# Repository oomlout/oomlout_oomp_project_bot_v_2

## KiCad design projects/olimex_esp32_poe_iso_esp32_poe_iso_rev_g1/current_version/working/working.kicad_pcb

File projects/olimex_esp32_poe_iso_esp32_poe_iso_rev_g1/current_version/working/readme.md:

# esp32_poe_iso
 
## summary 
* id: olimex_esp32_poe_iso_esp32_poe_iso_rev_g1
* user: olimex
* name: esp32_poe_iso
* board: esp32_poe_iso_rev_g1
* repo: https://github.com/OLIMEX/ESP32-POE-ISO
* src_file_repo_kicad_pcb: HARDWARE/ESP32-PoE-ISO-Rev.G1/ESP32-PoE-ISO_Rev_G1.kicad_pcb
* src_file_repo_kicad_pcb_link: https://github.com/OLIMEX/ESP32-POE-ISO/tree/master/HARDWARE/ESP32-PoE-ISO-Rev.G1/ESP32-PoE-ISO_Rev_G1.kicad_pcb

* src_file_repo_sch: HARDWARE/ESP32-PoE-ISO-Rev.G1/ESP32-PoE-ISO_Rev_G1.sch
* src_file_repo_sch_link: https://github.com/OLIMEX/ESP32-POE-ISO/tree/master/HARDWARE/ESP32-PoE-ISO-Rev.G1/ESP32-PoE-ISO_Rev_G1.sch
* full details link: https://github.com/oomlout/oomlout_oomp_project_bot_v_2/tree/main/projects/olimex_esp32_poe_iso_esp32_poe_iso_rev_g1/current_version/working

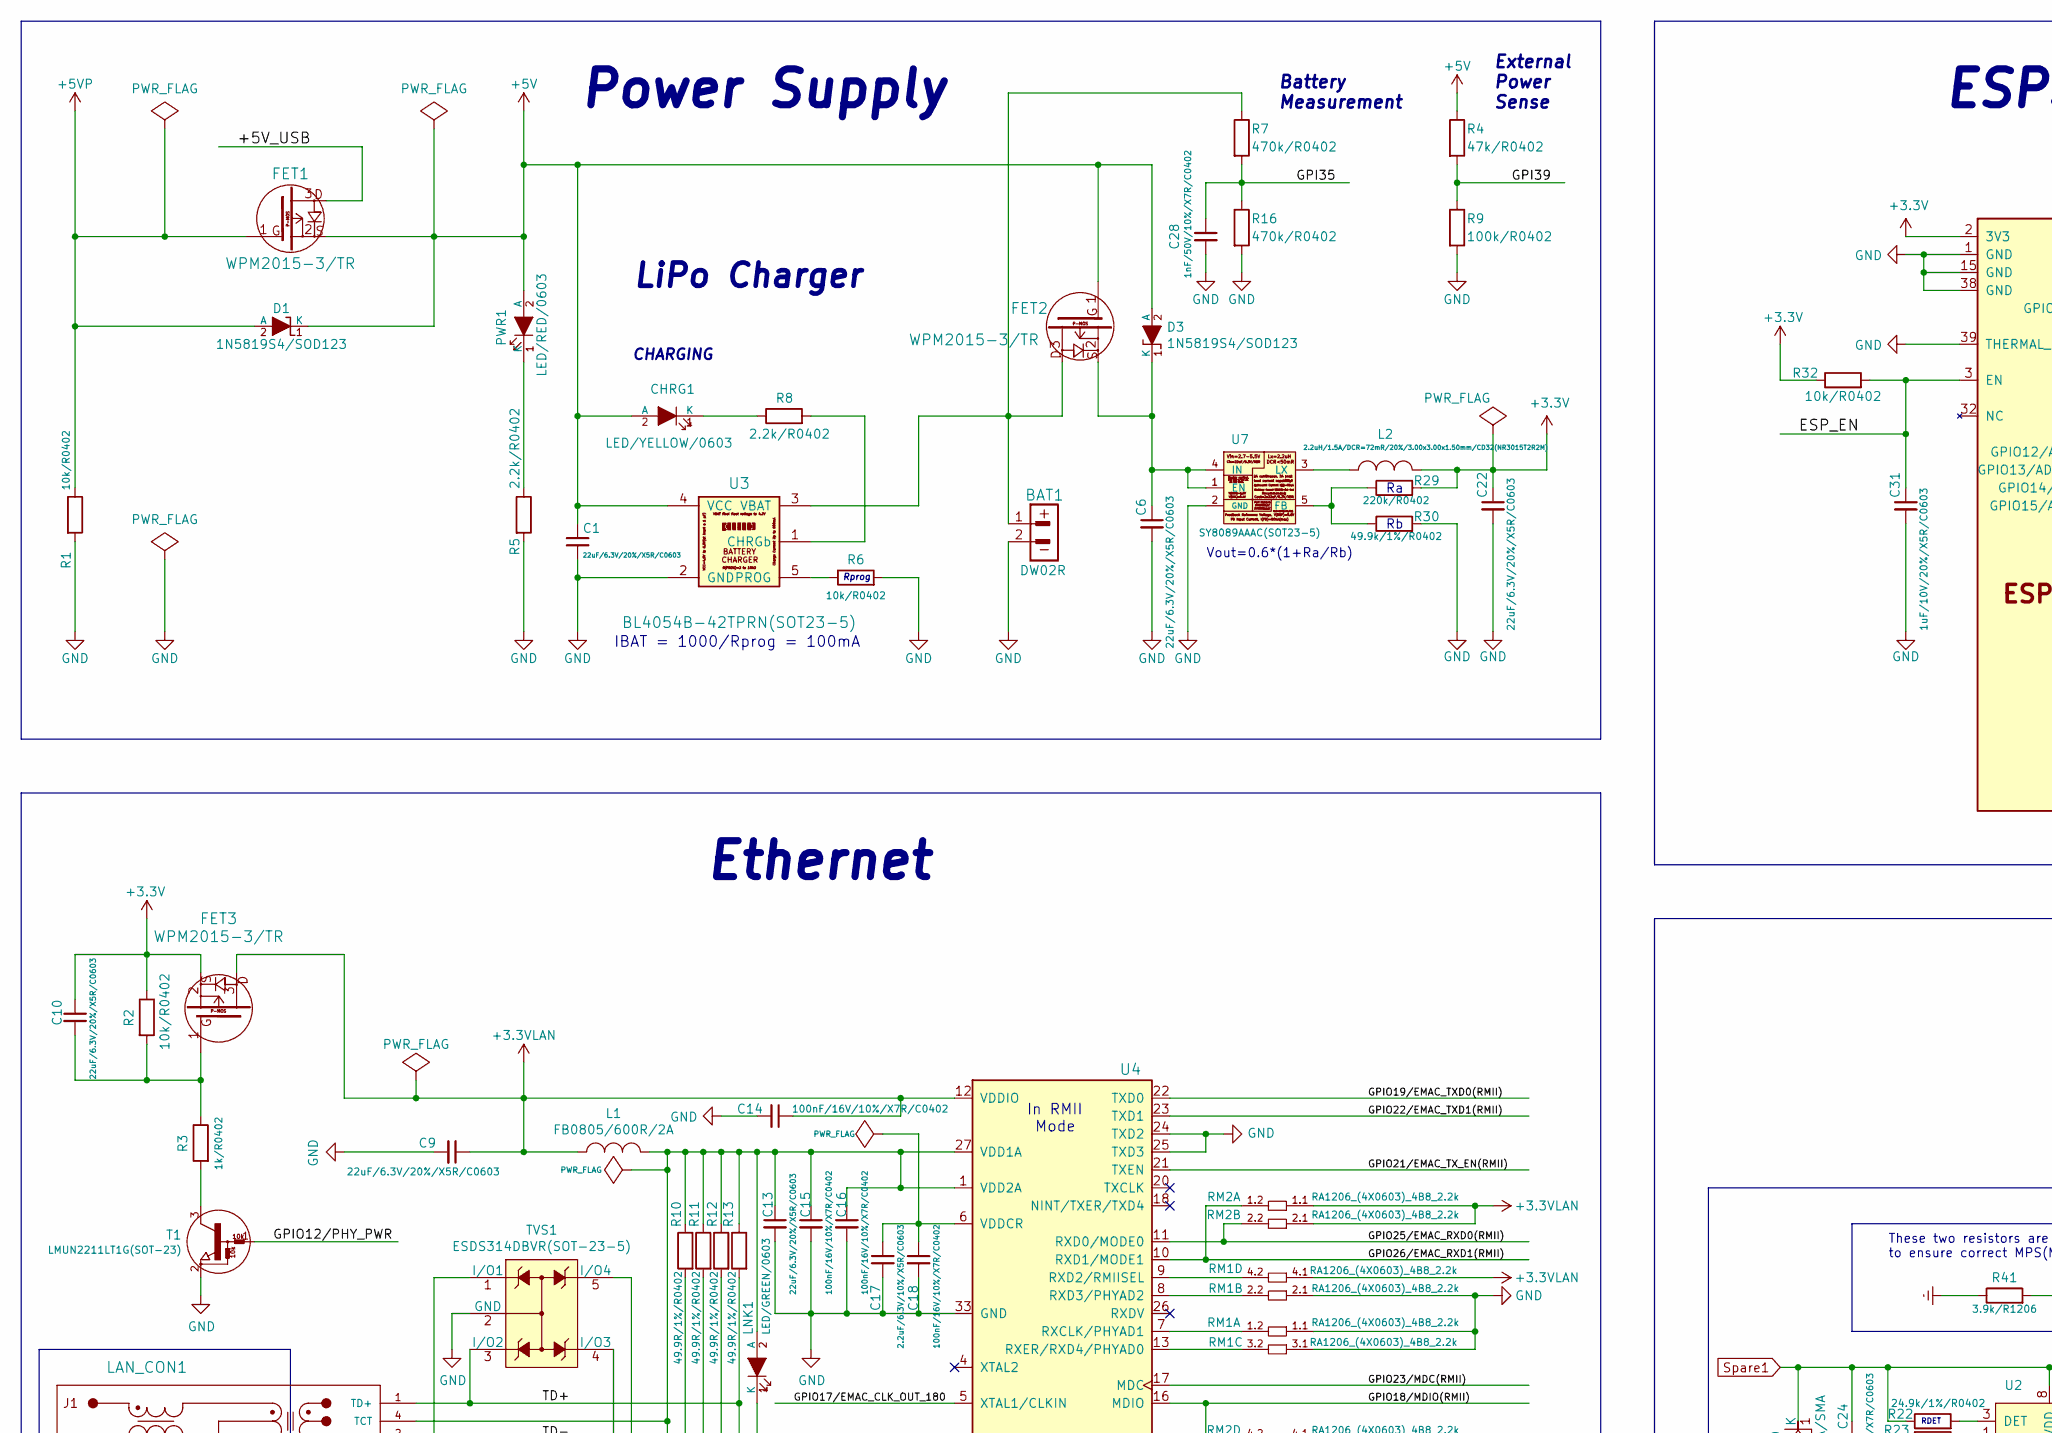
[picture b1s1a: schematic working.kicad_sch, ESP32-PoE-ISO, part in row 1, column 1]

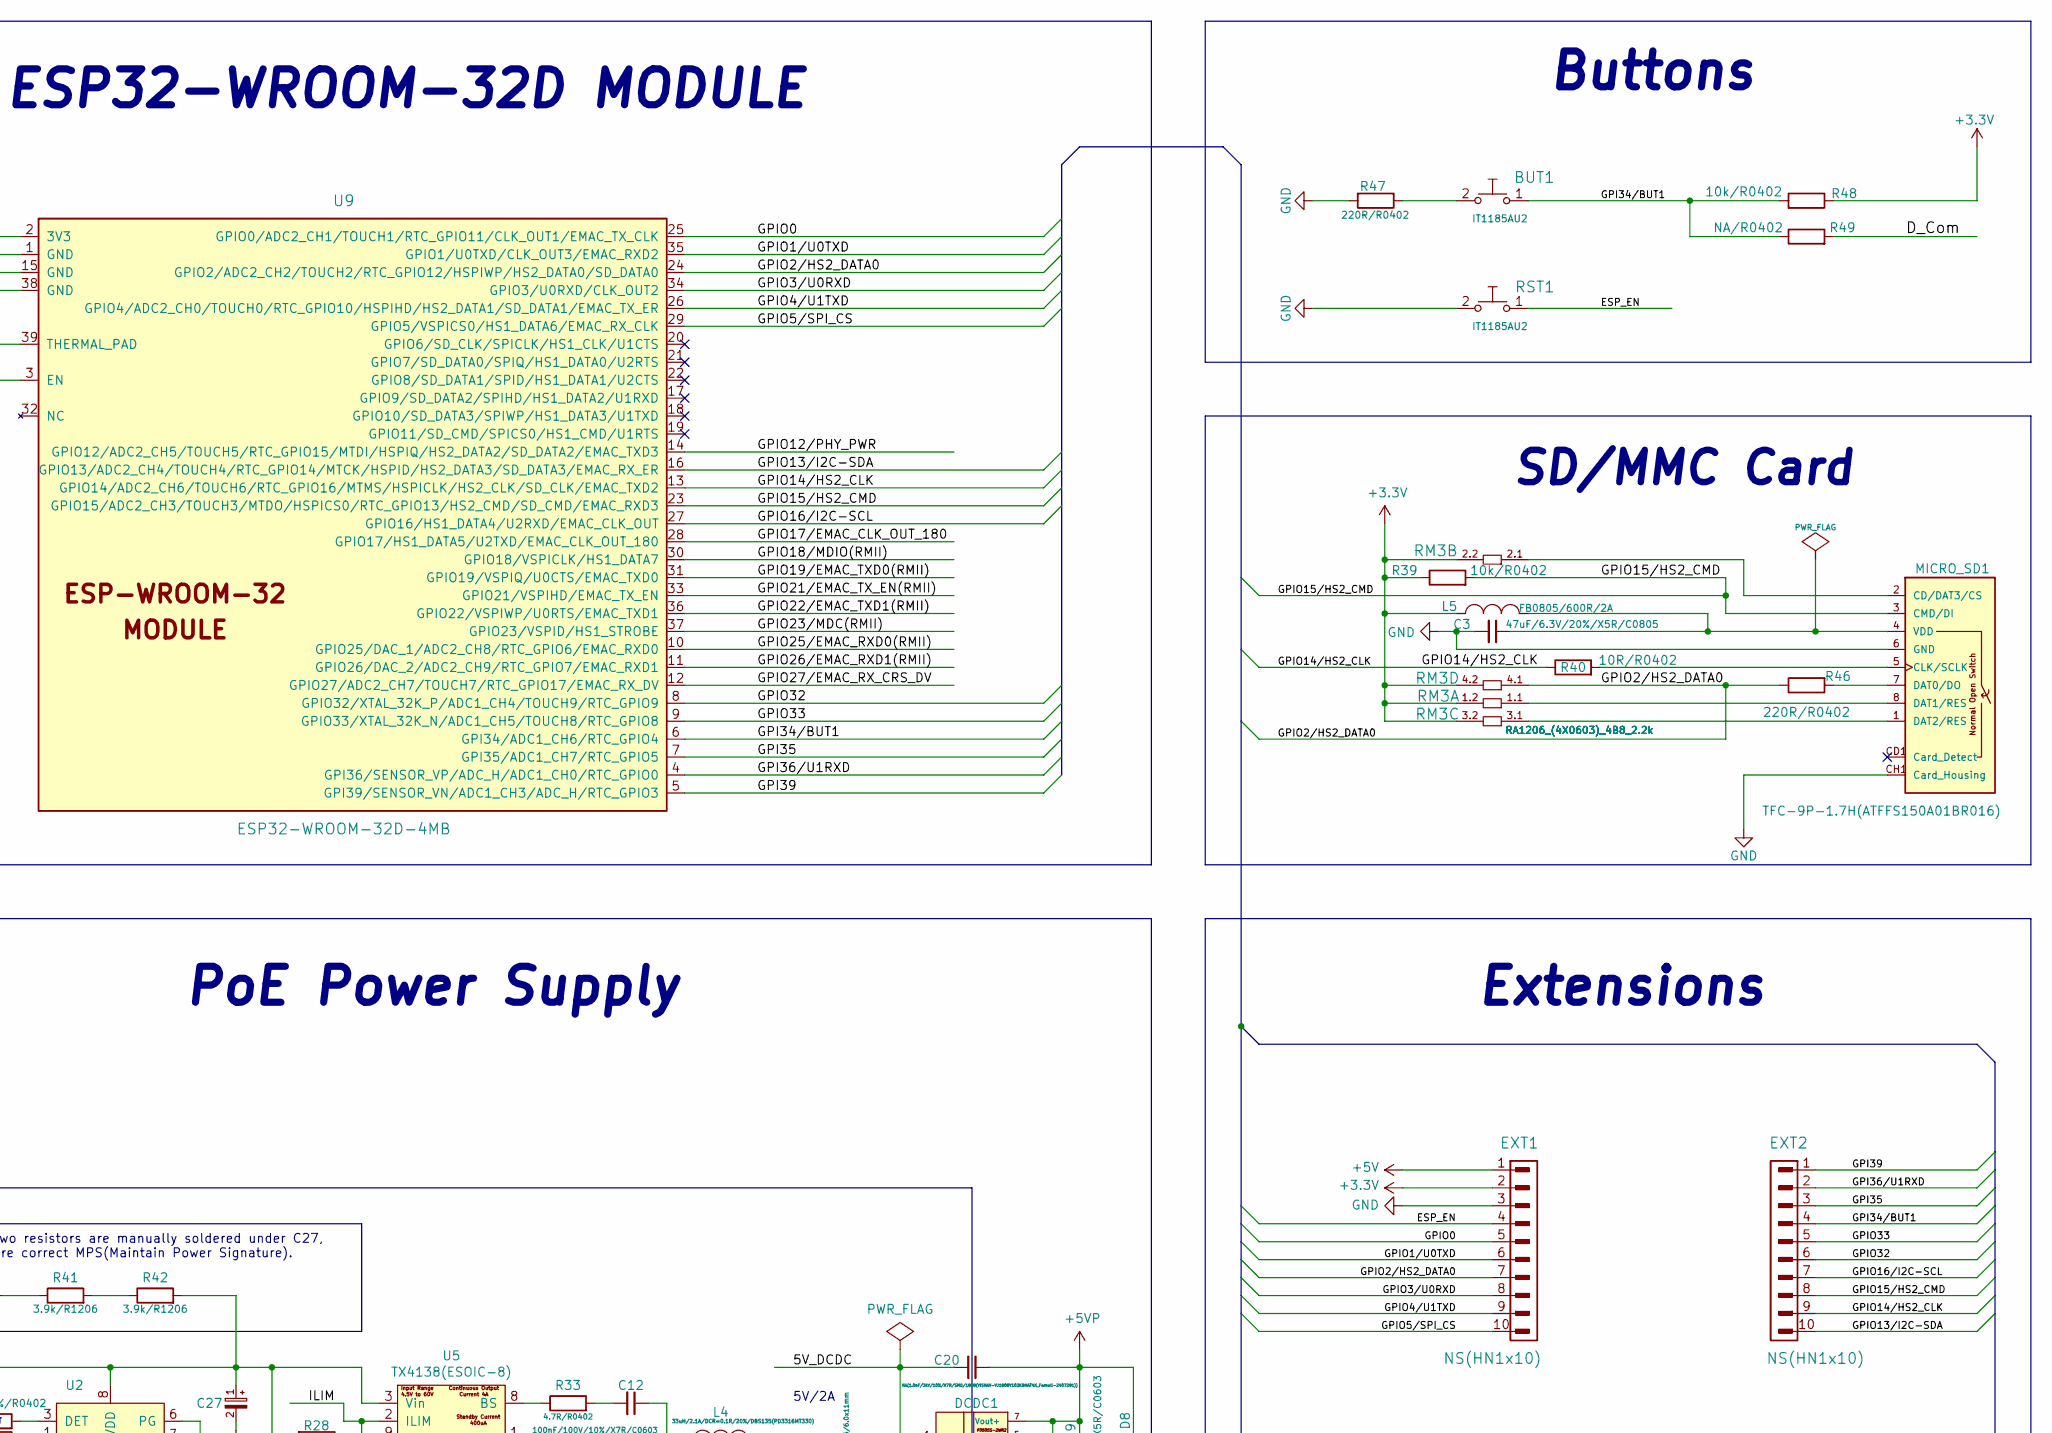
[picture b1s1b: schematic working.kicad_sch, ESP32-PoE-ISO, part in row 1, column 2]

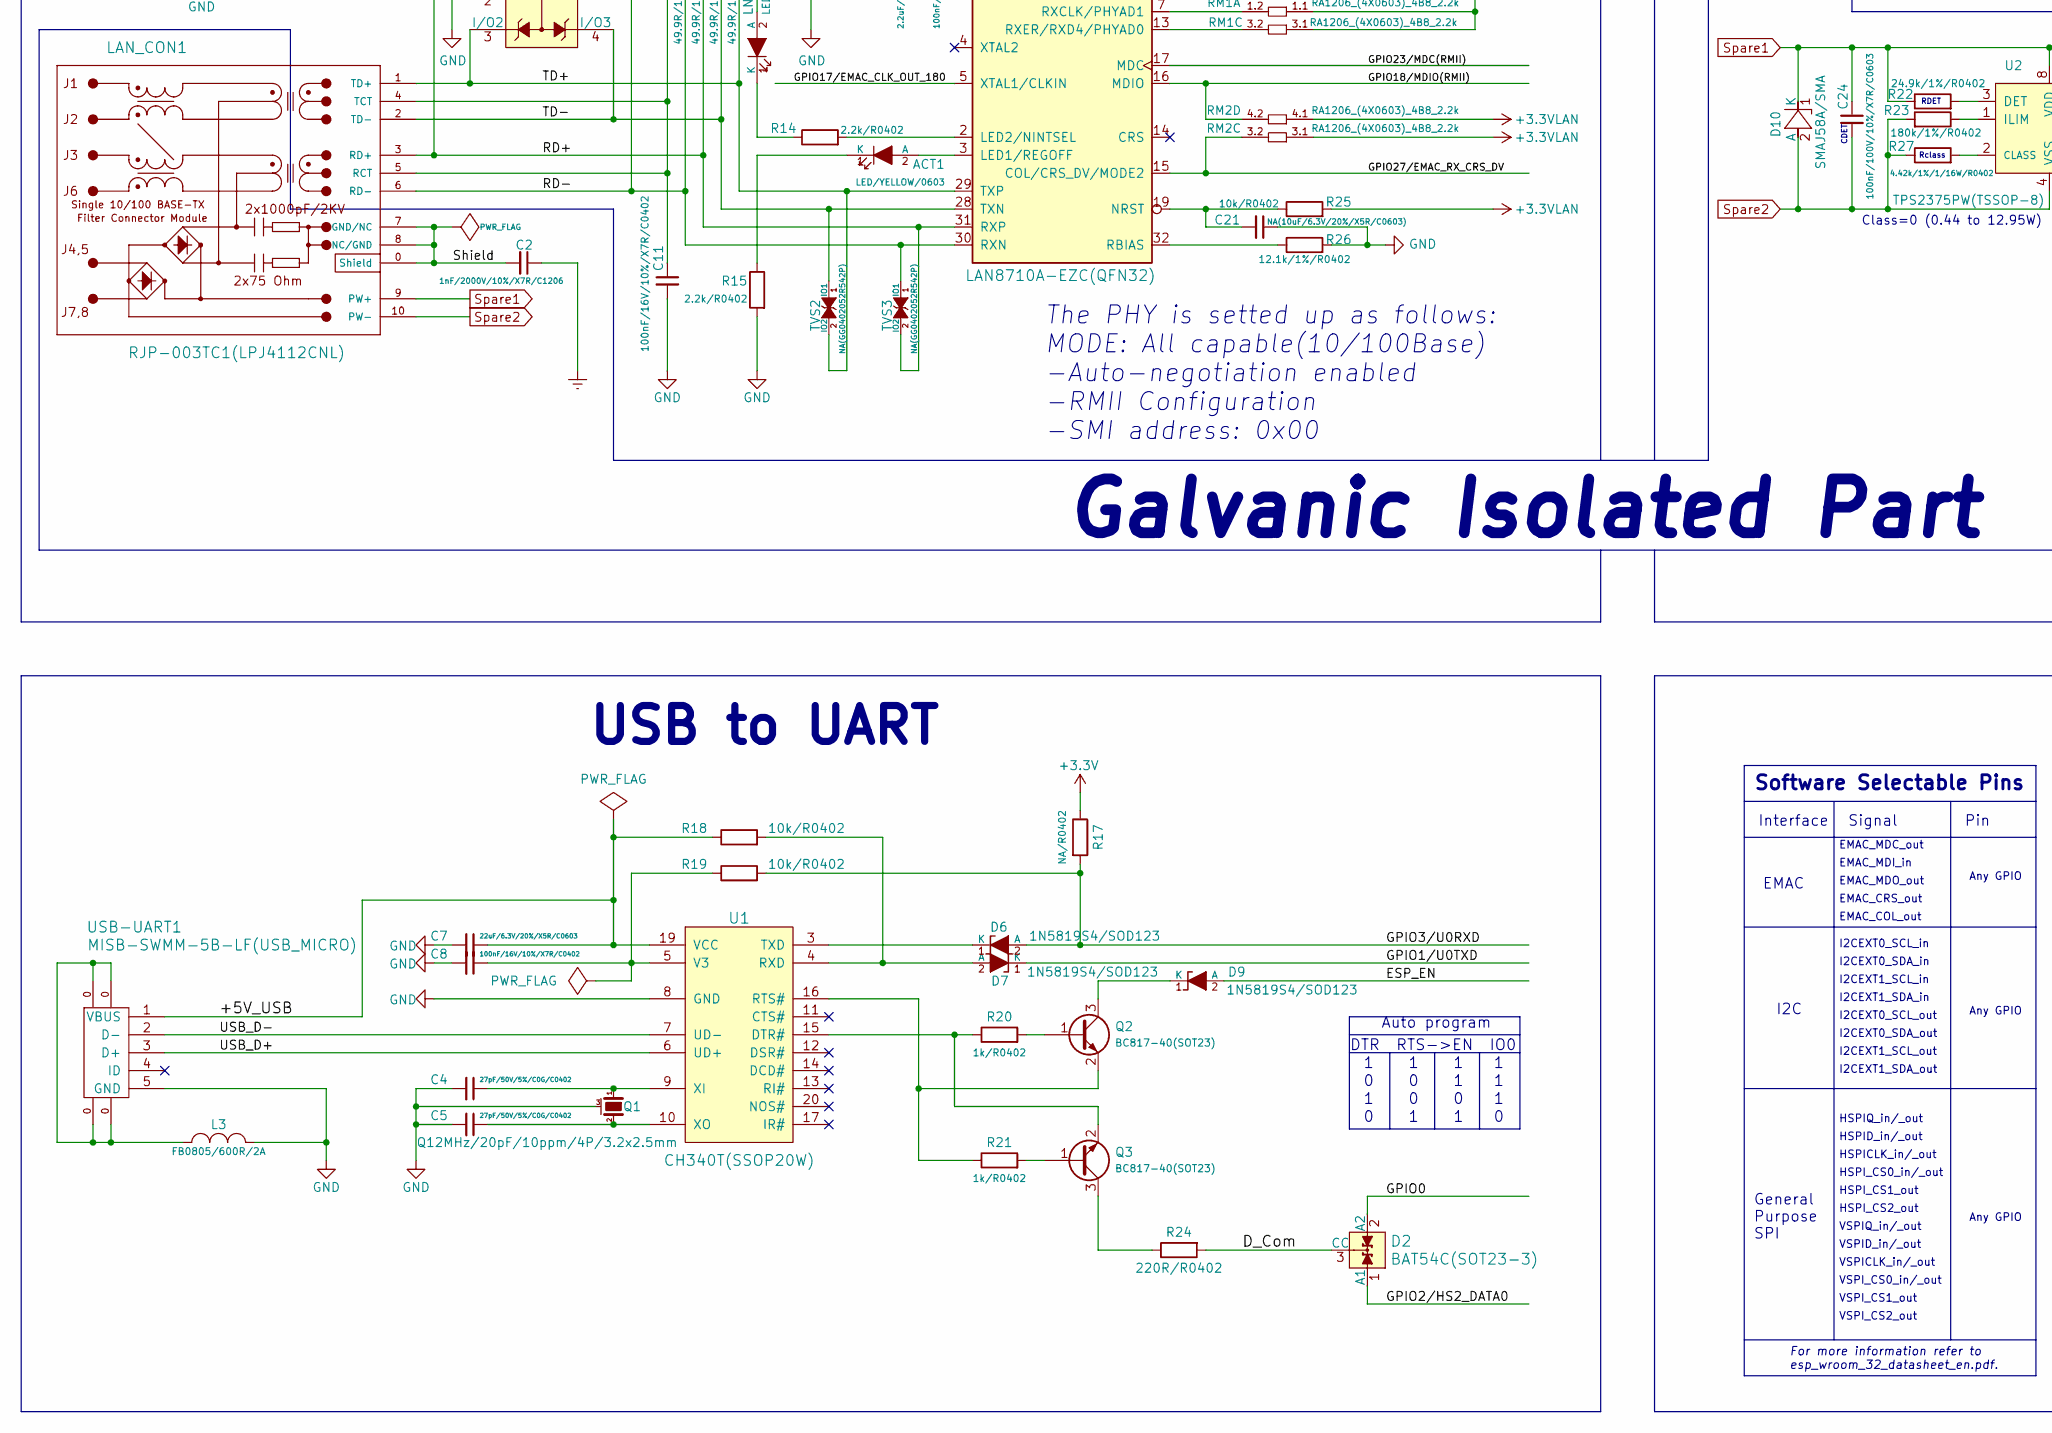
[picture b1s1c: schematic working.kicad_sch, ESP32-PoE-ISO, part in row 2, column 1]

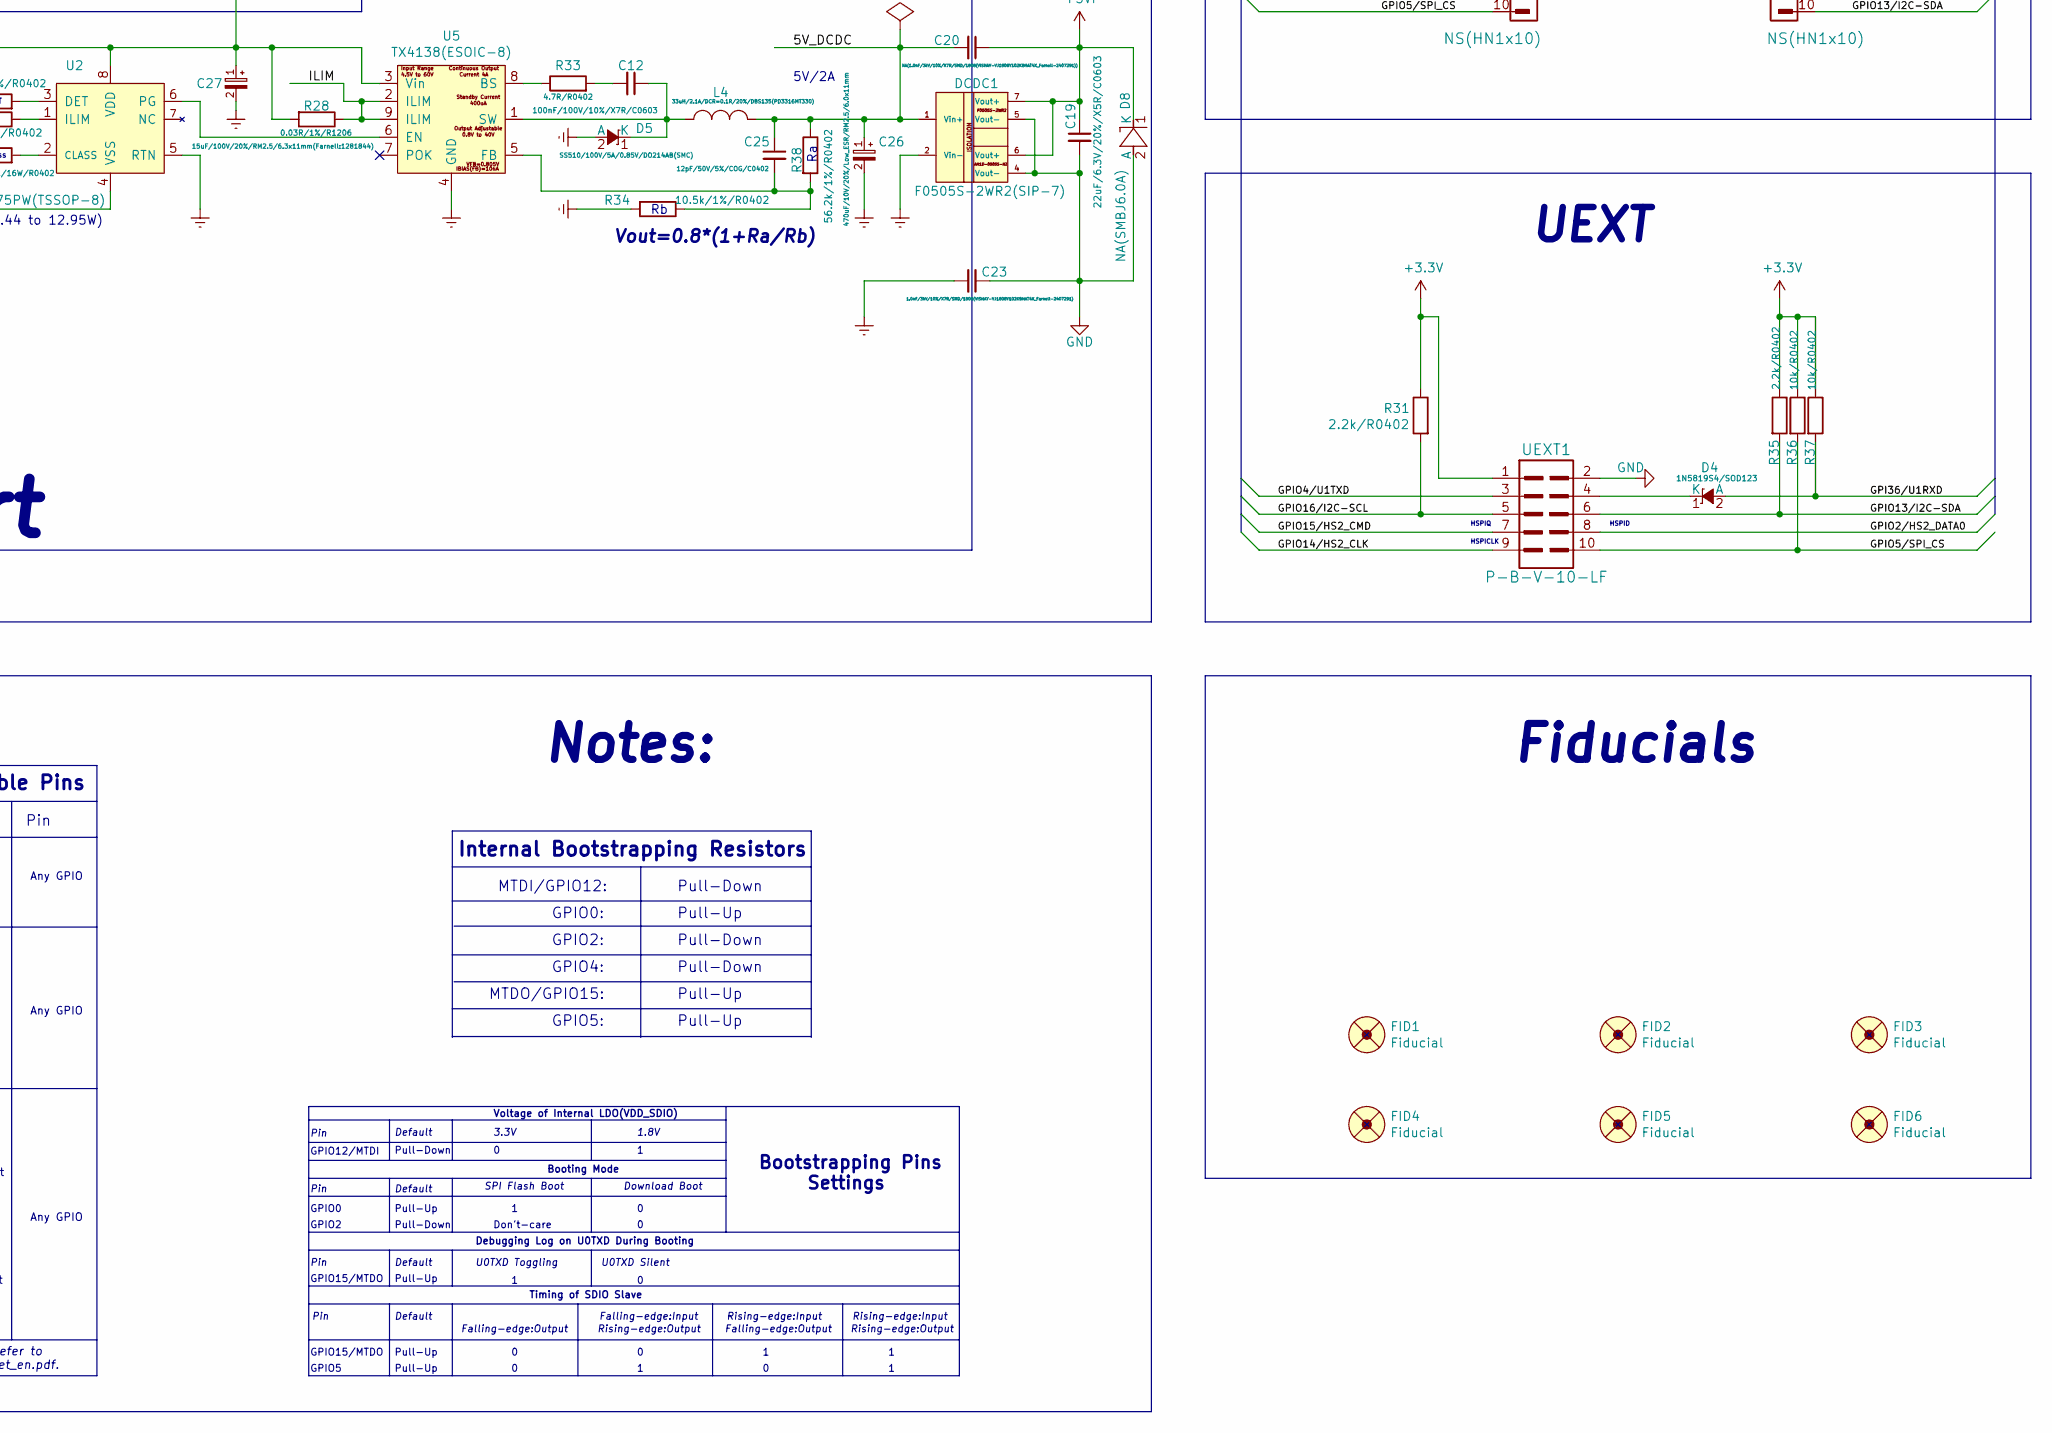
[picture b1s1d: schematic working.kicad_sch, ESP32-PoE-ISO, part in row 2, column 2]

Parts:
ACT1: LED/YELLOW/0603; LED_0603_KA
BAT1: DW02R; LIPO_BAT-CON2DW02R
BUT1: IT1185AU2; IT1185AU2_V2
C1, C6, C7, C9, C10, C13, C19, C22: 22uF/6.3V/20%/X5R/C0603; C_0603_5MIL_DWS
C2: 1nF/2000V/10%/X7R/C1206; C_1206_5MIL_DWS_ISO
C3: 47uF/6.3V/20%/X5R/C0805; C_0805_5MIL_DWS
C4, C5: 27pF/50V/5%/C0G/C0402; C_0402_5MIL_DWS
C8, C11, C14, C15, C16, C18: 100nF/16V/10%/X7R/C0402; C_0402_5MIL_DWS
C12, C24: 100nF/100V/10%/X7R/C0603; C_0603_5MIL_DWS
C17: 2.2uF/6.3V/10%/X5R/C0603; C_0603_5MIL_DWS
C20: NA(1.0nF/3kV/10%/X7R/SMD/1808(VISHAY-VJ1808Y102KB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; C_1808(4520)_5MIL_DWS_ISO
C21: NA(10uF/6.3V/20%/X5R/C0603); C_0603_5MIL_DWS
C23: 1.0nF/3kV/10%/X7R/SMD/1808(VISHAY-VJ1808Y102KBHAT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; C_1808(4520)_5MIL_DWS_ISO
C25: 12pF/50V/5%/COG/C0402; C_0402_5MIL_DWS
C26: 470uF/10V/20%/Low_ESR/RM2.5/6.0x11mm; CPOL-RM2.5mm_6.3x11mm_PTH
C27: 15uF/100V/20%/RM2.5/6.3x11mm(Farnell:1281844); CPOL-RM2.5mm_6.3x11mm_PTH
C28: 1nF/50V/10%/X7R/C0402; C_0402_5MIL_DWS
C31: 1uF/10V/20%/X5R/C0603; C_0603_5MIL_DWS
CHRG1: LED/YELLOW/0603; LED_0603_KA
D1, D3, D4, D6, D7, D9: 1N5819S4/SOD123; SOD-123_1C-2A_KA
D2: BAT54C(SOT23-3); SOT23-3
D5: SS510/100V/5A/0.85V/DO214AB(SMC); DO214AB(SMC)_1(K)-2(A)
D8: NA(SMBJ6.0A); DO214AA_1(K)-2(A)
D10: SMAJ58A/SMA; SMA-KA
DCDC1: F0505S-2WR2(SIP-7); SIP-7_Universal
EXT1, EXT2: NS(HN1x10); HN1x10
FET1, FET2, FET3: WPM2015-3/TR; SOT23
FID1, FID2, FID3, FID4, FID5, FID6: Fiducial; Fiducial1x3
L1, L3, L5: FB0805/600R/2A; L_0805_5MIL_DWS
L2: 2.2uH/1.5A/DCR=72mR/20%/3.00x3.00x1.50mm/CD32(NR3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; CD32
L4: 33uH/2.1A/DCR=0.1R/20%/DBS135(PD3316MT330); DBS135
LAN_CON1: RJP-003TC1(LPJ4112CNL)
LNK1: LED/GREEN/0603; LED_0603_KA
MICRO_SD1: TFC-9P-1.7H(ATFFS150A01BR016); uSD(TFC-9P-1.xH(ATFFS150A01BR016))
PWR1: LED/RED/0603; LED_0603_KA
Q1: Q12MHz/20pF/10ppm/4P/3.2x2.5mm; TSX-3.2x2.5mm_GND(3)
Q2, Q3: BC817-40(SOT23); SOT23
R1, R2, R6, R18, R19, R25, R32, R36, R37, R39, R48: 10k/R0402; R_0402_5MIL_DWS
R3, R20, R21: 1k/R0402; R_0402_5MIL_DWS
R4: 47k/R0402; R_0402_5MIL_DWS
R5, R8, R14, R15, R31, R35: 2.2k/R0402; R_0402_5MIL_DWS
R7, R16: 470k/R0402; R_0402_5MIL_DWS
R9: 100k/R0402; R_0402_5MIL_DWS
R10, R11, R12, R13: 49.9R/1%/R0402; R_0402_5MIL_DWS
R17, R49: NA/R0402; R_0402_5MIL_DWS
R22: 24.9k/1%/R0402; R_0402_5MIL_DWS
R23: 180k/1%/R0402; R_0402_5MIL_DWS
R24, R46, R47: 220R/R0402; R_0402_5MIL_DWS
R26: 12.1k/1%/R0402; R_0402_5MIL_DWS
R27: 4.42k/1%/1/16W/R0402; R_0402_5MIL_DWS
R28: 0.03R/1%/R1206; R_1206_5MIL_DWS
R29: 220k/R0402; R_0402_5MIL_DWS
R30: 49.9k/1%/R0402; R_0402_5MIL_DWS
R33: 4.7R/R0402; R_0402_5MIL_DWS
R34: 10.5k/1%/R0402; R_0402_5MIL_DWS
R38: 56.2k/1%/R0402; R_0402_5MIL_DWS
R40: 10R/R0402; R_0402_5MIL_DWS
R41, R42: 3.9k/R1206; R_1206_5MIL_DWS
RM1, RM2, RM3: RA1206_(4X0603)_4B8_2.2k; R_MATRIX_4
RST1: IT1185AU2; IT1185AU2_V2
T1: LMUN2211LT1G(SOT-23); SOT23
TVS1: ESDS314DBVR(SOT-23-5); SOT-23-5
TVS2, TVS3: NA(GG0402052R542P); D_0402_5MIL_DWS
U1: CH340T(SSOP20W); SSOP-20W
U2: TPS2375PW(TSSOP-8); TSSOP-8_Pitch-0.65mm_Dimensions-4.40x3.00x1.20mm
U3: BL4054B-42TPRN(SOT23-5); SOT-23-5
U4: LAN8710A-EZC(QFN32); QFN32_EP(33)_5.00x5.00x0.90mm_Pitch_0.50mm
U5: TX4138(ESOIC-8); ESOIC-8
U7: SY8089AAAC(SOT23-5); SOT-23-5
U9: ESP32-WROOM-32D-4MB; ESP-WROOM-32_MODULE
UEXT1: P-B-V-10-LF; GBH-254-SMT-10
USB-UART1: MISB-SWMM-5B-LF(USB_MICRO); USB-MICRO_MISB-SWMM-5B_LF

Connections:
+3.3VLAN: C9.1, C14.1, FET3.3, L1.1, R25.2, RM1.4.1, RM2.1.1, RM2.2.1, RM2.3.1, RM2.4.1, U4.12 (VDDIO)
+3V3: C10.1, C22.1, EXT1.2, FET3.2, L2.2, L5.1, R2.1, R17.1, R29.2, R31.1, R32.1, R35.1, R36.1, R37.1, R39.1, R48.1, RM3.1.2, RM3.2.2, RM3.3.2, RM3.4.2, U9.2 (3V3), UEXT1.1
+5V: C1.1, CHRG1.2 (A), D1.1 (K), D3.2 (A), EXT1.1, FET1.2, FET2.1, PWR1.2 (A), R4.1, U3.4 (VCC)
+5VP: C19.1, C20.1, D1.2 (A), D8.1 (K), DCDC1.6 (Vout+), DCDC1.7 (Vout+), FET1.1, R1.1
/5V_DCDC: C20.2, C25.1, C26.1 (+), DCDC1.1 (Vin+), L4.2, R38.1
/+5V_USB: C7.1, FET1.3, R18.1, U1.19 (VCC), USB-UART1.1 (VBUS)
/D_Com: D2.3 (CC), R24.2, R49.2
/ESP_EN: C31.1, D9.2 (A), EXT1.4, R32.2, RST1.1, U9.3 (EN)
/GPI34/BUT1: BUT1.1, EXT2.4, R48.2, R49.1, U9.6 (GPI34/ADC1_CH6/RTC_GPIO4)
/GPI35: C28.1, EXT2.3, R7.2, R16.1, U9.7 (GPI35/ADC1_CH7/RTC_GPIO5)
/GPI36/U1RXD: D4.2 (A), EXT2.2, R37.2, U9.4 (GPI36/SENSOR_VP/ADC_H/ADC1_CH0/RTC_GPIO0)
/GPI39: EXT2.1, R4.2, R9.1, U9.5 (GPI39/SENSOR_VN/ADC1_CH3/ADC_H/RTC_GPIO3)
/GPIO0: D2.2 (A2), EXT1.5, U9.25 (GPIO0/ADC2_CH1/TOUCH1/RTC_GPIO11/CLK_OU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)
/GPIO1/U0TXD: D7.1 (K), EXT1.6, U9.35 (GPIO1/U0TXD/CLK_OUT3/EMAC_RXD2)
/GPIO2/HS2_DATA0: D2.1 (A1), EXT1.7, R46.1, RM3.4.1, U9.24 (GPIO2/ADC2_CH2/TOUCH2/RTC_GPIO12/HSPIWP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), UEXT1.8
/GPIO3/U0RXD: D6.2 (A), EXT1.8, R17.2, R19.2, U9.34 (GPIO3/U0RXD/CLK_OUT2)
/GPIO4/U1TXD: EXT1.9, U9.26 (GPIO4/ADC2_CH0/TOUCH0/RTC_GPIO10/HSPIHD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), UEXT1.3
/GPIO5/SPI_CS: EXT1.10, R36.2, U9.29 (GPIO5/VSPICS0/HS1_DATA6/EMAC_RX_CLK), UEXT1.10
/GPIO12/PHY_PWR: T1.1 (B), U9.14 (GPIO12/ADC2_CH5/TOUCH5/RTC_GPIO15/MTDI/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)
/GPIO13/I2C-SDA: EXT2.10, R35.2, U9.16 (GPIO13/ADC2_CH4/TOUCH4/RTC_GPIO14/MTCK/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), UEXT1.6
/GPIO14/HS2_CLK: EXT2.9, R40.1, U9.13 (GPIO14/ADC2_CH6/TOUCH6/RTC_GPIO16/MTMS/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), UEXT1.9
/GPIO15/HS2_CMD: EXT2.8, MICRO_SD1.3 (CMD/DI), R39.2, U9.23 (GPIO15/ADC2_CH3/TOUCH3/MTDO/HSPICS0/RTC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), UEXT1.7
/GPIO16/I2C-SCL: EXT2.7, R31.2, U9.27 (GPIO16/HS1_DATA4/U2RXD/EMAC_CLK_OUT), UEXT1.5
/GPIO17/EMAC_CLK_OUT_180: U4.5 (XTAL1/CLKIN), U9.28 (GPIO17/HS1_DATA5/U2TXD/EMAC_CLK_OUT_180)
/GPIO18/MDIO(RMII): RM2.4.2, U4.16 (MDIO), U9.30 (GPIO18/VSPICLK/HS1_DATA7)
/GPIO19/EMAC_TXD0(RMII): U4.22 (TXD0), U9.31 (GPIO19/VSPIQ/U0CTS/EMAC_TXD0)
/GPIO21/EMAC_TX_EN(RMII): U4.21 (TXEN), U9.33 (GPIO21/VSPIHD/EMAC_TX_EN)
/GPIO22/EMAC_TXD1(RMII): U4.23 (TXD1), U9.36 (GPIO22/VSPIWP/U0RTS/EMAC_TXD1)
/GPIO23/MDC(RMII): U4.17 (MDC), U9.37 (GPIO23/VSPID/HS1_STROBE)
/GPIO25/EMAC_RXD0(RMII): RM2.2.2, U4.11 (RXD0/MODE0), U9.10 (GPIO25/DAC_1/ADC2_CH8/RTC_GPIO6/EMAC_RX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)
/GPIO26/EMAC_RXD1(RMII): RM2.1.2, U4.10 (RXD1/MODE1), U9.11 (GPIO26/DAC_2/ADC2_CH9/RTC_GPIO7/EMAC_RX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)
/GPIO27/EMAC_RX_CRS_DV: RM2.3.2, U4.15 (COL/CRS_DV/MODE2), U9.12 (GPIO27/ADC2_CH7/TOUCH7/RTC_GPIO17/EMAC_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)
/GPIO32: EXT2.6, U9.8 (GPIO32/XTAL_32K_P/ADC1_CH4/TOUCH9/RTC_G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)
/GPIO33: EXT2.5, U9.9 (GPIO33/XTAL_32K_N/ADC1_CH5/TOUCH8/RTC_G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)
/ILIM: R28.1, U5.2 (ILIM), U5.9 (ILIM)
/RD+: LAN_CON1.3 (RD+), R11.2, TVS1.1 (I/O1), TVS3.2 (IO2), U4.31 (RXP)
/RD-: LAN_CON1.6 (RD-), R10.2, TVS1.5 (I/O4), TVS3.1 (IO1), U4.30 (RXN)
/Shield: C2.2, LAN_CON1.0 (Shield), LAN_CON1.7 (GND/NC), LAN_CON1.8 (NC/GND)
/TD+: LAN_CON1.1 (TD+), R13.2, TVS1.3 (I/O2), TVS2.2 (IO2), U4.29 (TXP)
/TD-: LAN_CON1.2 (TD-), R12.2, TVS1.4 (I/O3), TVS2.1 (IO1), U4.28 (TXN)
/USB_D+: U1.6 (UD+), USB-UART1.3 (D+)
/USB_D-: U1.7 (UD-), USB-UART1.2 (D-)
Earth: C2.1, C23.2, C26.2 (-), C27.2 (-), D5.2 (A), DCDC1.2 (Vin-), R34.2, R41.1, U2.5 (RTN), U5.4 (GND)
GND: BAT1.2, C1.2, C3.2, C4.2, C5.2, C6.2, C7.2, C8.2, C9.2, C11.2, C13.2, C14.2, C15.2, C16.2, C17.2, C18.2, C19.2, C21.1, C22.2, C23.1, C28.2, C31.2, D8.2 (A), DCDC1.4 (Vout-), DCDC1.5 (Vout-), EXT1.3, L3.2, MICRO_SD1.6 (GND), MICRO_SD1.CH1 (Card_Housing), Q1.3 (case), R1.2, R5.2, R6.2, R9.2, R15.2, R16.2, R26.2, R30.2, R47.2, RM1.1.1, RM1.2.1, RM1.3.1, RST1.2, T1.2 (E), TVS1.2 (GND), U1.8 (GND), U3.2 (GND), U4.24 (TXD2), U4.25 (TXD3), U4.33 (GND), U7.2 (GND), U9.1 (GND), U9.15 (GND), U9.38 (GND), U9.39 (THERMAL_PAD), UEXT1.2, USB-UART1.5 (GND)
unnamed: ACT1.1 (K), R15.1
unnamed: ACT1.2 (A), U4.3 (LED1/REGOFF)
unnamed: BAT1.1, FET2.3, R7.1, U3.3 (VBAT)
unnamed: BUT1.2, R47.1
unnamed: C3.1, L5.2, MICRO_SD1.4 (VDD)
unnamed: C4.1, Q1.1, U1.9 (XI)
unnamed: C5.1, Q1.2, U1.10 (XO)
unnamed: C6.1, D3.1 (K), FET2.2, U7.1 (EN), U7.4 (IN)
unnamed: C8.1, R19.1, U1.5 (V3)
unnamed: C10.2, FET3.1, R2.2, R3.1
unnamed: C11.1, C13.1, C15.1, C16.1, L1.2, LAN_CON1.4 (TCT), LAN_CON1.5 (RCT), LNK1.2 (A), R10.1, R11.1, R12.1, R13.1, U4.1 (VDD2A), U4.27 (VDD1A)
unnamed: C12.1, D5.1 (K), L4.1, U5.1 (SW)
unnamed: C12.2, R33.2
unnamed: C17.1, C18.1, U4.6 (VDDCR)
unnamed: C21.2, R25.1, U4.19 (NRST)
unnamed: C25.2, R34.1, R38.2, U5.5 (FB)
unnamed: CHRG1.1 (K), R8.1
unnamed: D4.1 (K), UEXT1.4
unnamed: D6.1 (K), U1.3 (TXD)
unnamed: D7.2 (A), R18.2, U1.4 (RXD)
unnamed: D9.1 (K), Q2.3 (C)
unnamed: L2.1, U7.3 (LX)
unnamed: L3.1, USB-UART1.0
unnamed: LNK1.1 (K), R14.1
unnamed: MICRO_SD1.1 (DAT2/RES), RM3.3.1
unnamed: MICRO_SD1.2 (CD/DAT3/CS), RM3.2.1
unnamed: MICRO_SD1.5 (CLK/SCLK), R40.2
unnamed: MICRO_SD1.7 (DAT0/DO), R46.2
unnamed: MICRO_SD1.8 (DAT1/RES), RM3.1.1
unnamed: PWR1.1 (K), R5.1
unnamed: Q2.1 (B), R20.2
unnamed: Q2.2 (E), R21.1, U1.16 (RTS#)
unnamed: Q3.1 (B), R21.2
unnamed: Q3.2 (E), R20.1, U1.15 (DTR#)
unnamed: Q3.3 (C), R24.1
unnamed: R3.2, T1.3 (C)
unnamed: R6.1, U3.5 (PROG)
unnamed: R8.2, U3.1 (CHRGb)
unnamed: R14.2, U4.2 (LED2/NINTSEL)
unnamed: R22.2, U2.3 (DET)
unnamed: R23.1, U2.1 (ILIM)
unnamed: R26.1, U4.32 (RBIAS)
unnamed: R27.2, U2.2 (CLASS)
unnamed: R29.1, R30.1, U7.5 (FB)
unnamed: R33.1, U5.8 (BS)
unnamed: R41.2, R42.1
unnamed: RM1.1.2, U4.7 (RXCLK/PHYAD1)
unnamed: RM1.2.2, U4.8 (RXD3/PHYAD2)
unnamed: RM1.3.2, U4.13 (RXER/RXD4/PHYAD0)
unnamed: RM1.4.2, U4.9 (RXD2/RMIISEL)
unnamed: U2.6 (PG), U5.6 (EN)
Spare1: C24.1, C27.1 (+), D10.1 (K), LAN_CON1.9 (PW+), R22.1, R28.2, R42.2, U2.8 (VDD), U5.3 (Vin)
Spare2: C24.2, D10.2 (A), LAN_CON1.10 (PW-), R23.2, R27.1, U2.4 (VSS)

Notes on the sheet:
Software Selectable Pins
EMAC_MDC_out
The PHY is setted up as follows: MODE: All capable(10/100Base) -Auto-negotiation enabled -RMII Configuration -SMI address: 0x00
CDET
Pull-Up
Voltage of Internal LDO(VDD_SDIO)
HSPICLK
GPIO15/MTDO
U0TXD Silent
Rising-edge:Output
U0TXD Toggling
IBAT = 1000/Rprog = 100mA
VSPID_in/_out
Debugging Log on U0TXD During Booting
SPI Flash Boot
EMAC_COL_out
GPIO2:
I2CEXT0_SDA_out
Booting Mode
Rising-edge:Input
HSPI_CS2_out
I2CEXT1_SDA_out
Default
3.3V
VSPI_CS2_out
Falling-edge:Input
CHARGING
GPIO0:
HSPID_in/_out
HSPI_CS0_in/_out
General Purpose SPI
I2CEXT0_SCL_out
VSPICLK_in/_out
HSPIQ
HSPIQ_in/_out
Internal Bootstrapping Resistors
Pull-Down
GPIO5:
GPIO12/MTDI
Pin

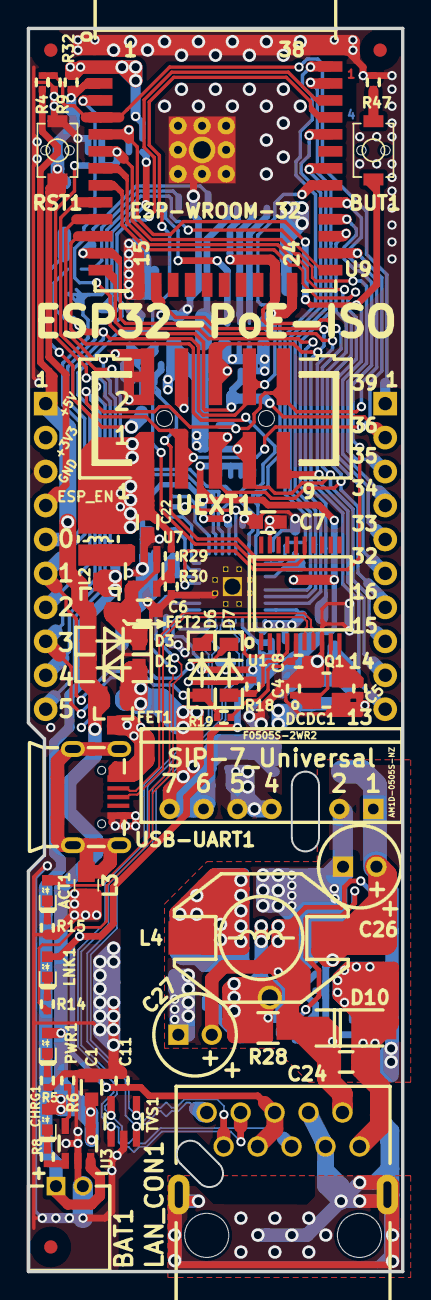
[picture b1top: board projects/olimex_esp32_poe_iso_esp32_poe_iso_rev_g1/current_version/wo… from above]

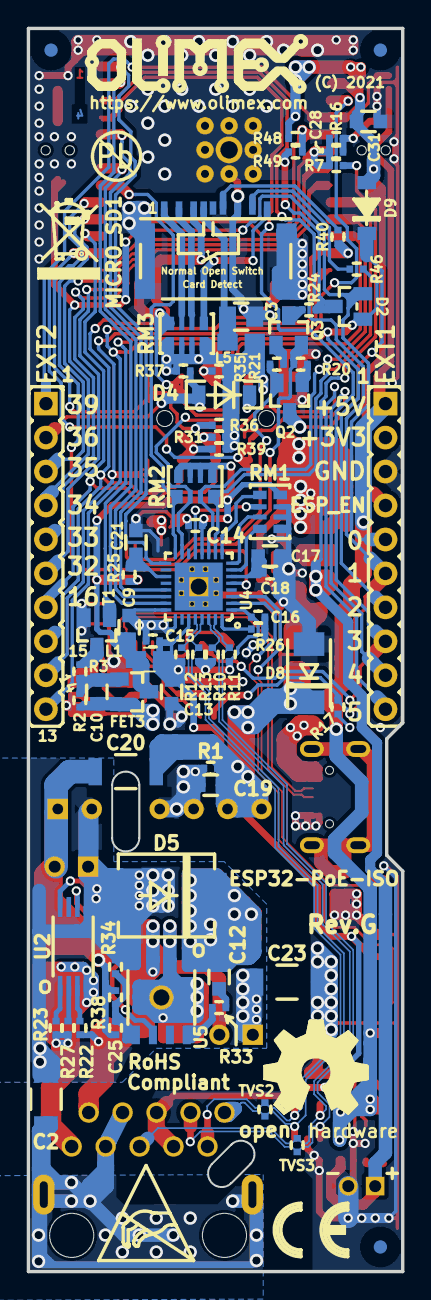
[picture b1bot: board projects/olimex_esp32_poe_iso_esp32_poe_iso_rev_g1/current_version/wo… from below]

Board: 4 copper layers, 28.0 x 93.0 mm, 136 parts (79 on the bottom side), 96 nets.

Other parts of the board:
Drill_Slot1, Drill_Slot3: 2 mm; Mounting_hole_2_mm
Logo_OSHW: LOGO_OPENHARDWARE_8x8
Logo_Olimex: OLIMEX_LOGO_TB
Sign_Antistatic: Val**; LOGO_ANTISTATIC_1
Sign_CE: CE_Sign
Sign_PB-Free: LOGO_PBFREE
Sign_RecycleBin: LOGO_RECYCLEBIN_1

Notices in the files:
projects/olimex_esp32_poe_iso_esp32_poe_iso_rev_g1/current_version/working/working.kicad_pcb:
(C) 2021
projects/olimex_esp32_pro_esp32_pro_rev_b/current_version/working/working.kicad_pcb:
(C) 2018
